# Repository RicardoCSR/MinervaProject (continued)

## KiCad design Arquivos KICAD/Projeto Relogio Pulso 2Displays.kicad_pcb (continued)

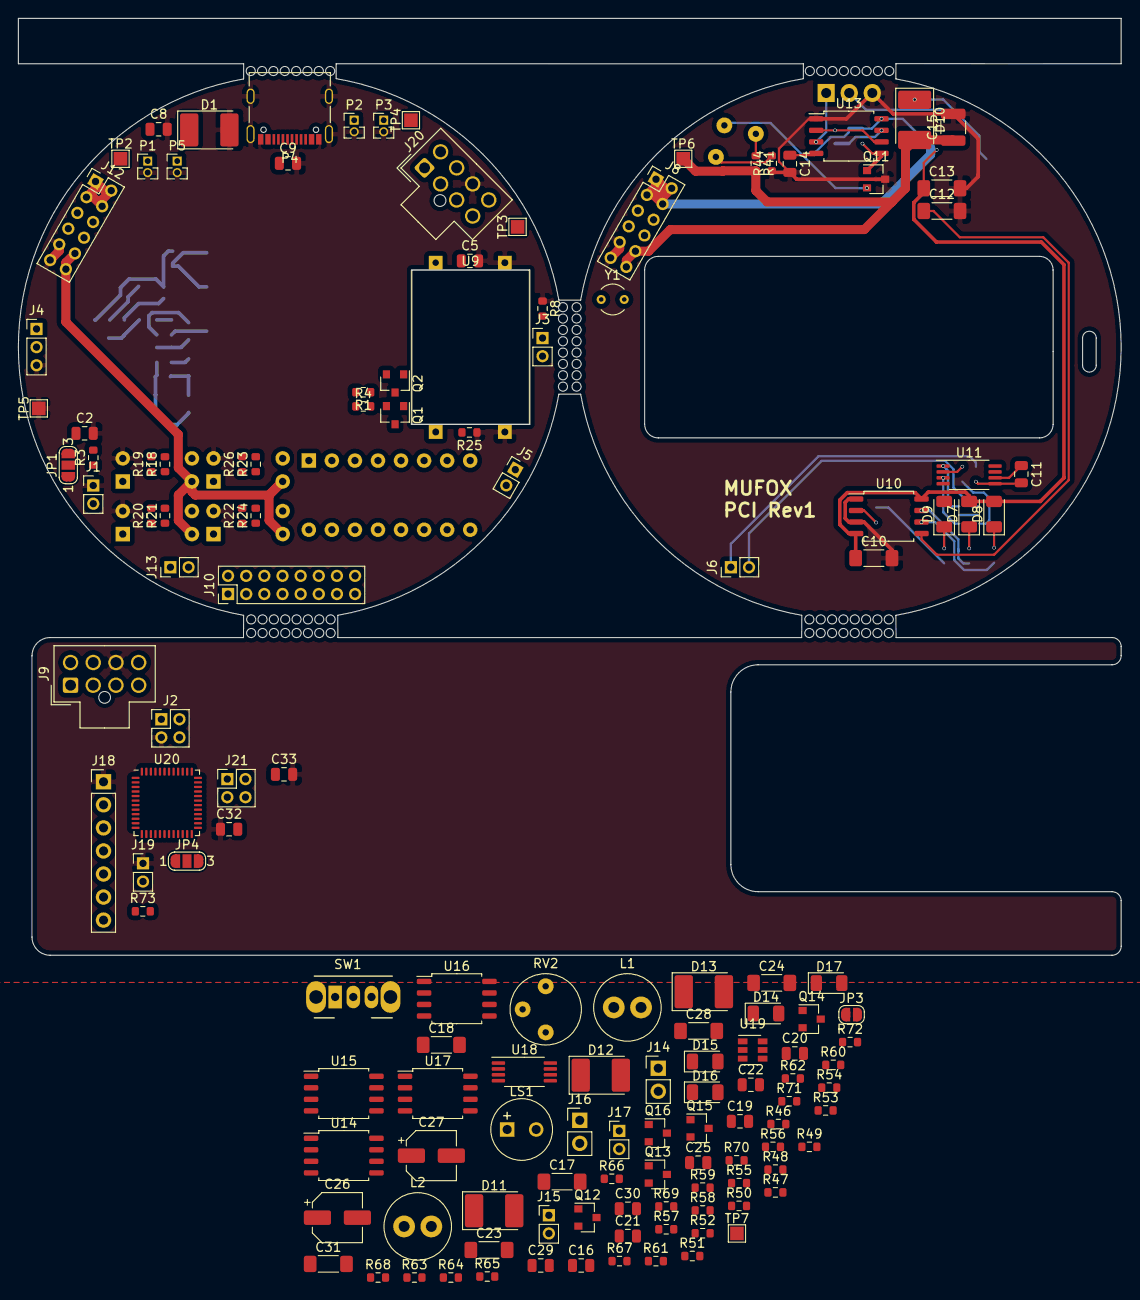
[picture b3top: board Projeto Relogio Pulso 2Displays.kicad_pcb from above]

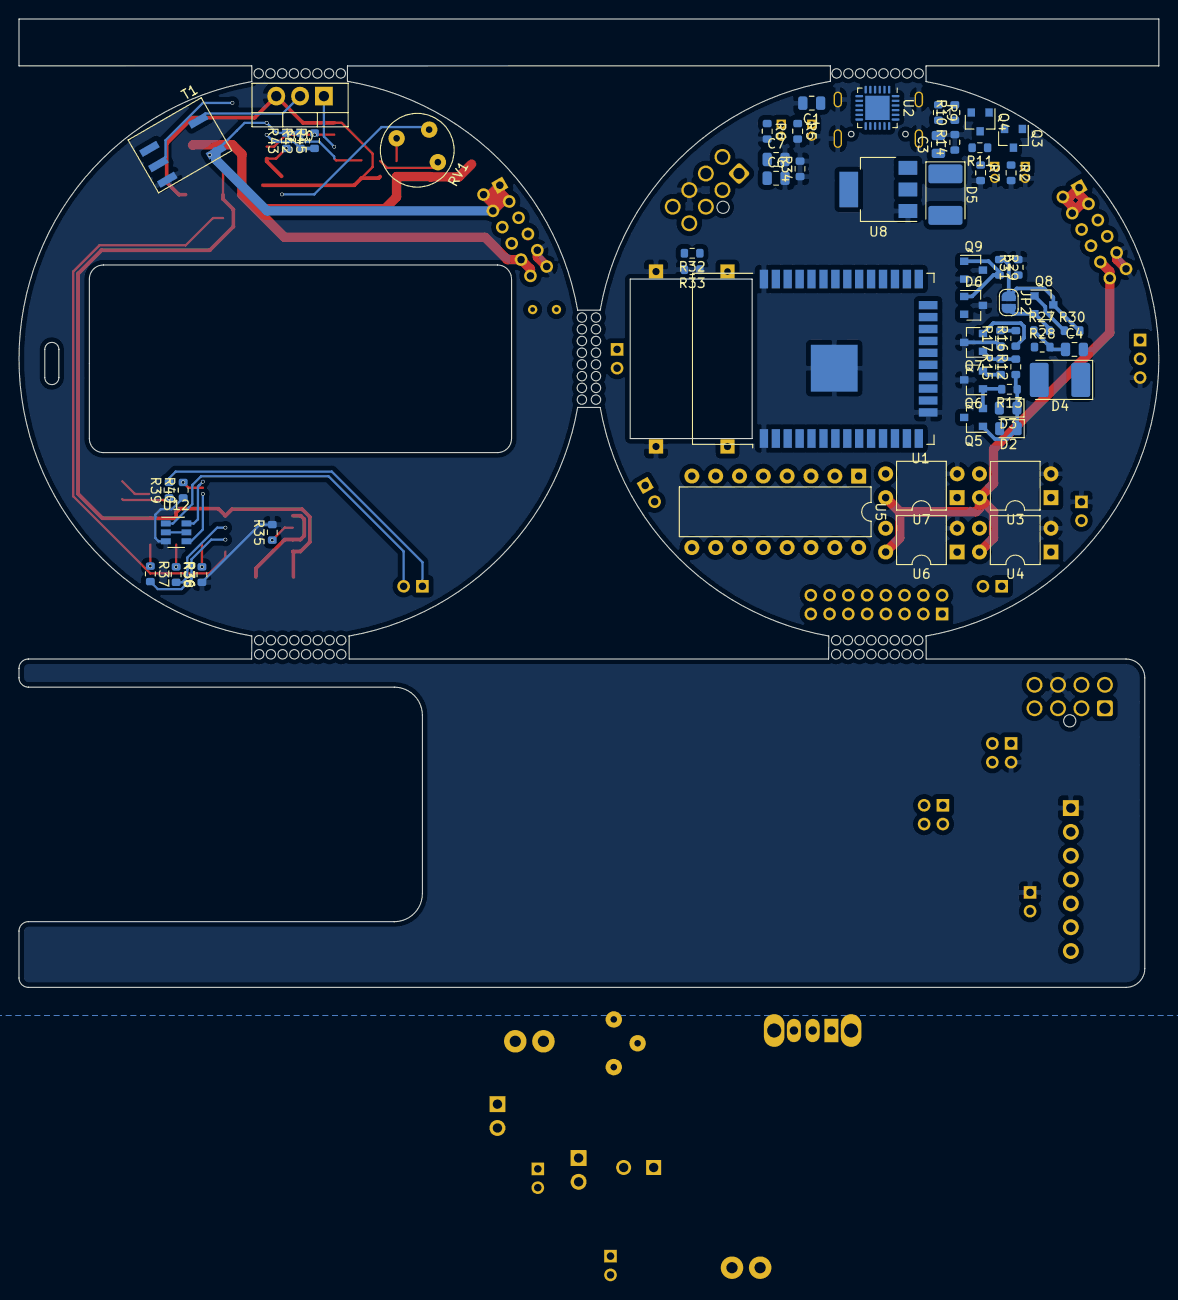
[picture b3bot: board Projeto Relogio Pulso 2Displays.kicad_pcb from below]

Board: 2 copper layers, 121.5 x 103.2 mm, 201 parts (60 on the bottom side), 159 nets.

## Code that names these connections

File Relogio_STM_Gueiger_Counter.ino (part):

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
R       Botao Hard Reset

PA0     Alimentacao LDR
PA1     Pino DC ST7789
PA2     Pino RST ST7789
PA3     Pino BLK ST7789
PA4     Geiger Sensor
PA5     Pino SCL ST7789 
PA6     LDR Sensor
PA7     Pino SDA ST7789
PA8     Pino Nixie A
PA9     Pino Nixie B
PA10    Pino Nixie C
PA11    Pino Nixie D
PA12    anode Nixie B
PA15    anode Nixie A

PB0     Nivel Bateria
PB1     Leitura Bat EN
PB2     
PB3     
PB4      
PB5     
PB6     **USART TX1
PB7     **USART RX1
PB8     Pino SCL BME280 // TESTAR
PB9     Pino SDA BME280 // TESTAR
PB10    
PB12    Botao Hibernar
PB13    Botao Menu
PB14    Botao Up
PB15    Botao Down

PC13    
PC14    anode Nixie C
PC15    anode Nixie D

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
// ------------------------------ CONFIGURACAO DOS PINOS DE SENSORES E DISPLAY --------

int ldrPinPower = PA0;          // Pino de alimentação do Sensor LDR
int ldrSensor = PA6;            // Pino do Sensor LDR
int geigerSensor = PA4;         // Pino do Sensor Geiger

int batteryLevel = PB0;         // Pino de Leitura da Bateria
int batteryCharger = PB1;       // Pino de Leitura Recarga Bateria

int dspPinPower = PA3;          // Pino de BackLight do Display ST7789

// ------------------------------ CORES DISPLAY STY7789 -------------------------------

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
volatile int repetitions = 2000;

#define BUTTON_SLEEP PB12       // Modo repouso * Apertar e Pressionar BUTTON_UP
#define BUTTON_MODE PB13        // Selecionar Modo Geiger, Clima ou Calendário
#define BUTTON_UP PB14          // Sobe no Menu 
#define BUTTON_DOWN PB15        // Desce no Menu 

#define batteryCharger PB1      // Pino EN Bateria

#define seaLevelPressure_HPA (1013.25)
#define BME280_ADDRESS 0x76
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
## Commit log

2022-02-26 Update README.md
    Atualização de dados do projeto.
2022-02-26 Add files via upload
    Plataforma utilizada:
    Arduino (STM32duino)
    Upload via ST-Link
    Plataforma de desenvolvimento Sublime Text 3
2022-03-02 Add files via upload
    Atualização do design projetado, design favorável a implementação e simplificação do código fonte
2022-03-02 Update README.md
    Atualização dos dados e implementação de novos conteúdos.
2022-03-05 Create Figma Link
    Arquivo de origem do site Figma, onde os design estão em desenvolvimento.
2022-03-05 Update README.md
    Inclusão dos pinos ESP32S e atualização para RMP.
2022-03-05 Update README.md
    Incluídos fontes utilizadas para o desenvolvimento do Projeto
2022-03-06 Update README.md
    Atualização de informações do projeto
2022-03-06 Add files via upload
    Fonte RedHatDisplay definidas no Figma, em avaliação no programa principal
2022-03-08 Add files via upload
    Atualização do Programa conforme o documento Figma Link
    Adicionados:
    Simbologia WiFi Level 1, 2 e 3
    Simbologia WiFi Offline
    Simbologia Baterias batteryStyleMode = 0;
    Simbologia Baterias batteryStyleMode = 1;
2022-03-09 Update README.md
    Inclusão do site de conversão de RGB888 para 565
2022-03-09 Delete RedHatDisplay_Regular_10.h
    Removido RedHatDisplay
2022-03-09 Delete RedHatDisplay_Regular_12.h
    Removido RedHatDisplay
2022-03-09 Delete RedHatDisplay_Regular_14.h
    Removido RedHatDisplay
2022-03-09 Add files via upload
    Inclusão dos arquivos de Lato Regular tamanho 10 e 12.
    Inclusão no programa das batteryStyleMode 2 e 3
    Inclusão no programa do Modo Geiger geigerStyleMode0 em progresso. 2046 ~ 2096.
2022-03-10 Add files via upload
    inclusão dosimeterStyleMode0 e paleta de cores atualizadas.
2022-03-11 Add files via upload
    Adicionado geigerGraphStyleMode0, WeatherStyleMode0(), tempGraphStyleMode0, humiGraphStyleMode0, presGraphStyleMode0
2022-03-13 Add files via upload
    Incluido calendarStyleMode0, timerStyleMode0, ajustTimeStyleMode0, ajustDataStyleMode0, ajustBrightStyleMode0
    Iniciado procedimento de correção de bugs operacionais configuração e alinhamento dos dados para apresentação dos dados as páginas gerados.
2022-03-13 Add files via upload
    Alterado PA4 e PA6 Sensor Gueiger e Sensor LDR
    Incluído ajustes do Menu Geiger, sendo incluido sistema de média no gráfico sem glitch de repetição.
2022-03-13 Update README.md
    Ajustes e correções
2022-03-18 Add files via upload
    Inclusão e teste de sequencia Nixie
2022-03-18 Add files via upload
    Inclusão e testes com Nixie
2022-03-29 Add files via upload
    Ajustes de escala e correção do Dosimeter.
2022-03-30 Add files via upload
    Inclusão do gráfico Geiger
2022-03-31 Add files via upload
    Ajustes do Modo GraphGeiger
2022-04-01 Add files via upload
    Continuidade GraphGeiger
2022-04-04 Add files via upload
    Adicionado gráficos de Temperatura, Umidade, e Pressão Atm. incluído pino EN para identificação do carregador e niveis de bateria.
    #Corrigir corte nos gráficos e incluir restauração dos dados após sair do Menu.
2022-04-04 Update README.md
    Inclusão da página web: https://thunkable.com/#/ criação de Aplicativos Android
2022-04-04 Add files via upload
    Teste e configuração para operação com ESP32
2022-04-05 Add files via upload
    Ajuste para testes e configuração da rede WiFi
2022-04-07 Add files via upload
    Testes e configurações
2022-04-08 Add files via upload
    Arquivos testes para configuração das páginas Web para ESP32 atualizadas para o WiFiManager
2022-04-08 Add files via upload
    Pinos e configuração para aplicação em PCB do ESP32 comunicação e gravação RS232
2022-04-09 Add files via upload
    Autalização e inclusão de novos elementos para a página Web
2022-04-10 Add files via upload
    Atualização e execução de layout HTML
2022-04-11 Add files via upload
    Atualização das páginas e imagens
2022-04-12 Add files via upload
    Atualização e complemento
2022-04-12 Delete Teste_WiFi_Communication.ino
    Movido para Pasta teste_WiFi_Communication
2022-04-14 Add files via upload
    Remoção da Função Nixie() sendo movimentada para o ARM ESP32
2022-04-16 Add files via upload
    Arquivos KiCad
2022-08-29 Delete Lato_bold_24.h
    Substituido pelo LatoReular_24.h
2022-08-29 Add files via upload
    Imagens utilizada no ILI9486
2022-08-29 Delete Relogio_STM_Gueiger_Counter.ino
    Substituido pelo Relogio_STM32_TFT_Nixie
2022-08-29 Update README.md
    Atualização do microcontrolador e pinos utilizados.
2022-08-29 Update README.md
    Atualização do RMP
2022-08-30 Add files via upload
    Inclusão das telas 1, 2 e 3
2022-10-19 Add files via upload
    Funcao Touch
2023-05-15 Add files via upload
    Incluido Smooth fonts
